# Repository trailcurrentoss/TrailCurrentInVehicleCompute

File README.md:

# TrailCurrent In-Vehicle Compute

Dockerized edge gateway with MQTT broker, tile server, and local dashboards. Part of the [TrailCurrent](https://trailcurrent.com) open-source vehicle platform.

## Quick Navigation

| I want to... | Go here |
|--------------|---------|
| Set up a development environment | [Development Setup](#development-setup) below |
| Build a deployment package | [Building Deployment Packages](#building-deployment-packages) below |
| Set up a new Raspberry Pi | [DOCS/RaspberryPiOneTimeSetup.md](DOCS/RaspberryPiOneTimeSetup.md) |
| Deploy or update a Pi | [PI_DEPLOYMENT.md](PI_DEPLOYMENT.md) |
| Set up Node-RED flows | [Node-RED Setup](#node-red-setup) below |
| Understand cloud OTA updates | [OTA_DEPLOYMENT_IMPLEMENTATION.md](OTA_DEPLOYMENT_IMPLEMENTATION.md#cloud-to-pi-ota-deployment-deployment-watcher) |

## Prerequisites

- **Docker Engine** (or Docker Desktop) with the `compose` plugin and `buildx`
- **Git**

---

## Development Setup

This gets your local development environment running with hot-reload and debugging enabled. All services build from local Dockerfiles for the host platform.

### Step 1: Clone and configure environment

```bash
git clone <REPO_URL>
cd TrailCurrentInVehicleCompute
git config core.hooksPath .githooks
docker buildx use default
cp .env.example .env
```

### Step 2: Generate secure random values

```bash
# Generate ENCRYPTION_KEY (64 character hex string)
openssl rand -hex 32

# Generate NODE_RED_CREDENTIAL_SECRET (128 character hex string)
openssl rand -hex 64
```

Copy these values into the corresponding fields in `.env`.

### Step 3: Edit `.env` and set your values

- `NODE_RED_ADMIN_USER` - Your Node-RED admin username
- `NODE_RED_ADMIN_PASSWORD` - Your desired admin password (plain text - auto-hashed at startup)
- `ENCRYPTION_KEY` - Paste the value from step 2
- `NODE_RED_CREDENTIAL_SECRET` - Paste the value from step 2
- `ADMIN_PASSWORD` - Strong password for system admin access
- `MQTT_USERNAME` - Username for MQTT broker
- `MQTT_PASSWORD` - Password for MQTT broker (plain text - auto-added to broker at startup)
- `TLS_CERT_HOSTNAME` - Your device's hostname (e.g., `trailcurrent01.local`)

### Step 4: Generate SSL certificates

```bash
./scripts/generate-certs.sh
# Select option 1 for Development or option 2 for Production
```

See [SSL Certificate Generation](#ssl-certificate-generation) for details.

### Step 5: Obtain map tiles

The tileserver requires a pre-generated mbtiles file to serve map data.

```bash
mkdir -p data/tileserver
# Place your tiles file at: data/tileserver/map.mbtiles
```

To generate tiles from OpenStreetMap data, use the **PbfTileConverter** utility:
[../../Utilities/PbfTileConverter](../../Utilities/PbfTileConverter)

Or copy `map.mbtiles` from an existing team member's machine.

### Step 6: Build and start in development mode

```bash
docker compose -f docker-compose.yml -f docker-compose.dev.yml up -d --build
```

The `--build` flag ensures all images are built from local Dockerfiles for your host platform. Development mode enables:
- Hot-reload for frontend and backend code changes
- Node.js debug port (9229) for VSCode debugger attachment
- MongoDB accessible on localhost:27017
- Node-RED accessible on localhost:1880
- Tileserver styles hot-reload

Containers will automatically:
- Generate the bcrypt hash for Node-RED from your plain password
- Create the mosquitto password file from your credentials
- Initialize all services with consistent credentials
- Mount the SSL certificates for HTTPS/MQTTS communication
- Load map tiles from the mbtiles file

### Verification Checklist

After startup, verify all services are healthy:

```bash
# All 7 containers should be running
docker compose ps

# Frontend loads
curl -k https://localhost/

# Tileserver healthy
curl http://localhost:8080/health

# Map style served
curl -s http://localhost:8080/styles/3d-dark/style.json | head -5

# Font glyphs available
curl -s -o /dev/null -w "%{http_code}" "http://localhost:8080/fonts/Noto%20Sans%20Regular/0-255.pbf"
# Expected: 200
```

**Access the web UI:** https://localhost (accept the self-signed certificate warning)

### Security Notes

- `.env` is in `.gitignore` - will never be committed
- Use strong, randomly generated passwords for all credentials
- All values in `.env.example` are placeholders only
- Passwords are auto-hashed/auto-configured at container startup

---

## Building Deployment Packages

For creating the offline zip that gets deployed to Raspberry Pis. The deployment pipeline builds Docker images for ARM64, packages them as tar files, and creates a self-contained zip.

```bash
# Build everything and create the zip
./create-deployment-package.sh --version=1.0.0
```

This will:
1. Build all 6 service images for `linux/arm64` (plus pull `mongo:7`)
2. Save images as `.tar` files in `images/`
3. Fetch MCU firmware from GitHub releases (if available)
4. Package everything into `trailcurrent-deployment-1.0.0.zip`

**Transfer and deploy to Pi:**
```bash
scp trailcurrent-deployment-1.0.0.zip trailcurrent@pi.local:~
# On the Pi:
unzip trailcurrent-deployment-1.0.0.zip && chmod +x deploy.sh && ./deploy.sh
```

See [PI_DEPLOYMENT.md](PI_DEPLOYMENT.md) for detailed deployment instructions.

---

## Project Structure

```
containers/          Dockerfiles for each service
  frontend/          nginx + MapLibre GL web UI
  backend/           Node.js Express API
  mosquitto/         Eclipse Mosquitto MQTT broker
  node-red/          Node-RED flow engine
  noderedproxy/      nginx HTTPS proxy for Node-RED
  tileserver/        Custom tile server (styles, fonts, sprites)
config/              Version-controlled service configurations
  mosquitto/         mosquitto.conf
  node-red/          settings.js, starter-flow.json, cloud-workflow.json
data/                Runtime data (gitignored)
  keys/              TLS certificates
  tileserver/        map.mbtiles
  node-red/          Node-RED flows
local_code/          Python host services (CAN-to-MQTT bridge, deployment watcher, OTA helpers)
scripts/             Utility scripts (cert generation)
```

**Docker Compose files:**
- `docker-compose.yml` — Production orchestration (7 services)
- `docker-compose.dev.yml` — Development overrides (hot-reload, debug ports)

---

## SSL Certificate Generation

The application uses TLS/SSL for secure communication. Certificates must be generated before running `docker compose up`. The `scripts/generate-certs.sh` script supports two modes:

### Quick Reference

```bash
# Interactive mode (prompts for selection)
./scripts/generate-certs.sh

# Non-interactive mode (development)
./scripts/generate-certs.sh 1

# Non-interactive mode (production)
./scripts/generate-certs.sh 2

# Using environment variable
CERT_MODE=2 ./scripts/generate-certs.sh

# Show help
./scripts/generate-certs.sh --help
```

### Development Certificates (Local Testing)

For local development with `localhost` or `127.0.0.1`:

```bash
./scripts/generate-certs.sh 1
```

**Development certificates include:**
- DNS names: `localhost`, plus your `TLS_CERT_HOSTNAME` from `.env`
- IP addresses: `127.0.0.1`, `::1` (IPv6 localhost)

**Access locally:**
```
https://localhost           - Frontend (HTTPS)
https://localhost:8443      - Node-RED (HTTPS)
```

Accept the self-signed certificate warning in your browser (one-time).

### Production Certificates (Deployment)

For deployed devices accessed from other machines on the network:

1. **Set your device's hostname** in `.env`:
   ```
   TLS_CERT_HOSTNAME=trailcurrent01.local
   ```

2. **Generate production certificates:**
   ```bash
   ./scripts/generate-certs.sh 2
   ```

3. **Install the CA certificate** (`data/keys/ca.crt`) on devices that will access the web UI.

4. **Access from the network:**
   ```
   https://trailcurrent01.local       - Web UI
   mqtts://trailcurrent01.local:8883  - MQTT broker
   ```

### Regenerating Certificates

Run the script anytime to regenerate. It will prompt before overwriting existing certificates and create backups.

```bash
./scripts/generate-certs.sh
docker compose restart
```

Certificates are automatically protected by `.gitignore`. Never commit them to version control.

---

## Docker

### Running Containers

```bash
# Development mode (hot-reload, debug ports) — always use --build to ensure local images
docker compose -f docker-compose.yml -f docker-compose.dev.yml up -d --build

# Production mode (after verification)
docker compose up -d --build
```

### Docker Networking

**MongoDB Access:**
- Services communicate via Docker's internal network: `mongodb:27017`
- MongoDB is NOT exposed to localhost (127.0.0.1)
- To access MongoDB from your host: `docker compose exec mongodb mongosh`

Docker containers use service names for inter-container communication.

### Data Persistence

The `data/` directory contains all persistent application data:

- **SSL certificates** (`data/keys/`) — Generated once, valid for 10 years
- **Map tiles** (`data/tileserver/map.mbtiles`) — Set up once, rarely updated
- **Node-RED flows** (`data/node-red/`) — User-created flows and settings
- **MongoDB** — Named volume `mongodb-data`, persists across rebuilds

**Never delete `data/` during updates** unless performing a complete reset. All data persists across container rebuilds.

**Updating the Application (No Data Loss):**
```bash
git pull
docker compose -f docker-compose.yml -f docker-compose.dev.yml up -d --build
# Certificates, .env, map tiles, and Node-RED flows are preserved
```

---

## Node-RED Setup

Node-RED bridges CAN bus messages to local MQTT topics that the PWA consumes. Flow templates are stored in `config/node-red/`.

### What the Starter Flow Does

- **Inbound:** Subscribes to `can/inbound`, routes by CAN identifier, and publishes parsed data to `local/*` topics:
  - Light status (8 channels) → `local/lights/{1-8}/status`
  - Temperature & humidity → `local/airquality/temphumid`
  - GPS coordinates, altitude, details, time → `local/gps/*`
- **Outbound:** Subscribes to `local/lights/{1-8}/command` (from PWA light toggles) and sends CAN messages to `can/outbound`
- **Test controls:** Manual inject nodes for toggling lights, setting brightness, and all-on/all-off

### Automatic Loading (First Startup)

On first startup, the backend automatically detects that Node-RED has no flows and injects the starter flow via the Node-RED Admin API. Existing installations with flows already present are not affected.

### Cloud Workflow (Auto-Injected)

When cloud synchronization is enabled in Settings, the backend automatically injects a "Cloud Workflow" tab into Node-RED that bridges messages between the local and cloud MQTT brokers:

- **Cloud → Local (Commands):** `rv/lights/N/command` → CAN toggle, `rv/thermostat/command` → local passthrough
- **Local → Cloud (Status):** Light status, air quality, GPS, energy, thermostat — each rate-limited to 30 msg/sec

The cloud workflow is automatically removed when cloud is disabled or the system config is reset. The template is at `config/node-red/cloud-workflow.json`.

### Manual Import (Existing Installations)

1. Open Node-RED at `https://<hostname>:8443`
2. Click the hamburger menu (top right) → **Import**
3. Select **Upload** and choose `config/node-red/starter-flow.json`
4. Click **Import**

### Configure MQTT Credentials

After importing, Node-RED needs MQTT credentials to connect to Mosquitto:

1. Double-click any MQTT node (e.g. "CAN Inbound")
2. Click the pencil icon next to **Local MQTT Broker**
3. Go to the **Security** tab
4. Enter your `MQTT_USERNAME` and `MQTT_PASSWORD` (same values from `.env`)
5. Click **Update**, then click the red **Deploy** button

The broker is pre-configured to connect to `mosquitto:8883` via Docker internal DNS with TLS.

---

## Debugging

### VSCode Node.js Debugger

The backend Node.js server can be debugged using VSCode's built-in debugger. The setup uses `--inspect-brk` to pause the application at startup, waiting for the debugger to attach before continuing execution.

#### Quick Start

1. **Open the project in VSCode** (if not already open)

2. **Start debugging:**
   - Open the Debug panel (Ctrl+Shift+D / Cmd+Shift+D)
   - Select "Backend Debug" from the dropdown
   - Click the green "Start Debugging" button (or press F5)

3. **What happens automatically:**
   - Docker containers start in development mode (`docker-compose -f docker-compose.yml -f docker-compose.dev.yml up`)
   - Backend container starts with `--inspect-brk=0.0.0.0:9229` (pauses at startup)
   - VSCode automatically attaches the debugger to port 9229
   - Application resumes and you can now set breakpoints

4. **Stop debugging:**
   - Press Shift+F5 or click the stop button in the debug panel
   - Docker containers are automatically stopped (`docker-compose down`)

#### Manual Debugging (Without VSCode Integration)

```bash
# Start containers in development mode
docker compose -f docker-compose.yml -f docker-compose.dev.yml up

# In VSCode, attach manually:
# - Open Debug panel (Ctrl+Shift+D)
# - Select "Backend Debug"
# - Click "Start Debugging" (F5)
```

#### Debugging Configuration

The debugging setup is configured in `.vscode/launch.json`:

```json
{
  "name": "Backend Debug",
  "type": "node",
  "request": "attach",
  "port": 9229,
  "address": "localhost",
  "restart": true,
  "skipFiles": ["<node_internals>/**"],
  "outFiles": ["${workspaceFolder}/containers/backend/src/**/*.js"]
}
```

#### Troubleshooting

**"Connection refused" error:**
- Ensure containers are running: `docker compose ps`
- Check backend container logs: `docker compose logs backend`
- Verify port 9229 is exposed: `docker compose port backend 9229`

**Breakpoints not being hit:**
- Verify the file path matches exactly (case-sensitive on Linux)
- Check development mode: `docker compose config | grep "NODE_ENV"`

**Backend container exits immediately:**
- Check logs: `docker compose logs backend`
- Ensure `.env` file is set up correctly
- Verify MongoDB: `docker compose logs mongodb`

**Mosquitto or other containers failing to start:**
- Check logs: `docker compose logs mosquitto`
- Certificate permissions: `chmod 644 data/keys/*.key data/keys/*.crt data/keys/*.pem`

**Port conflicts:**
- Clean up: `docker system prune -f --volumes`
- Verify no containers running: `docker ps -a`
- Restart Docker: `sudo systemctl restart docker`

#### Tips for Effective Debugging

1. **Breakpoint in startServer()** in `src/index.js` to debug initialization
2. **Route breakpoints** in route handlers (e.g., `src/routes/thermostat.js`)
3. **MQTT debugging** via breakpoints in `src/mqtt.js`
4. **Database debugging** via breakpoints in `src/db/init.js`
5. **Conditional breakpoints**: Right-click a breakpoint to set conditions
6. **Logpoints**: Right-click line number to log values without pausing

---

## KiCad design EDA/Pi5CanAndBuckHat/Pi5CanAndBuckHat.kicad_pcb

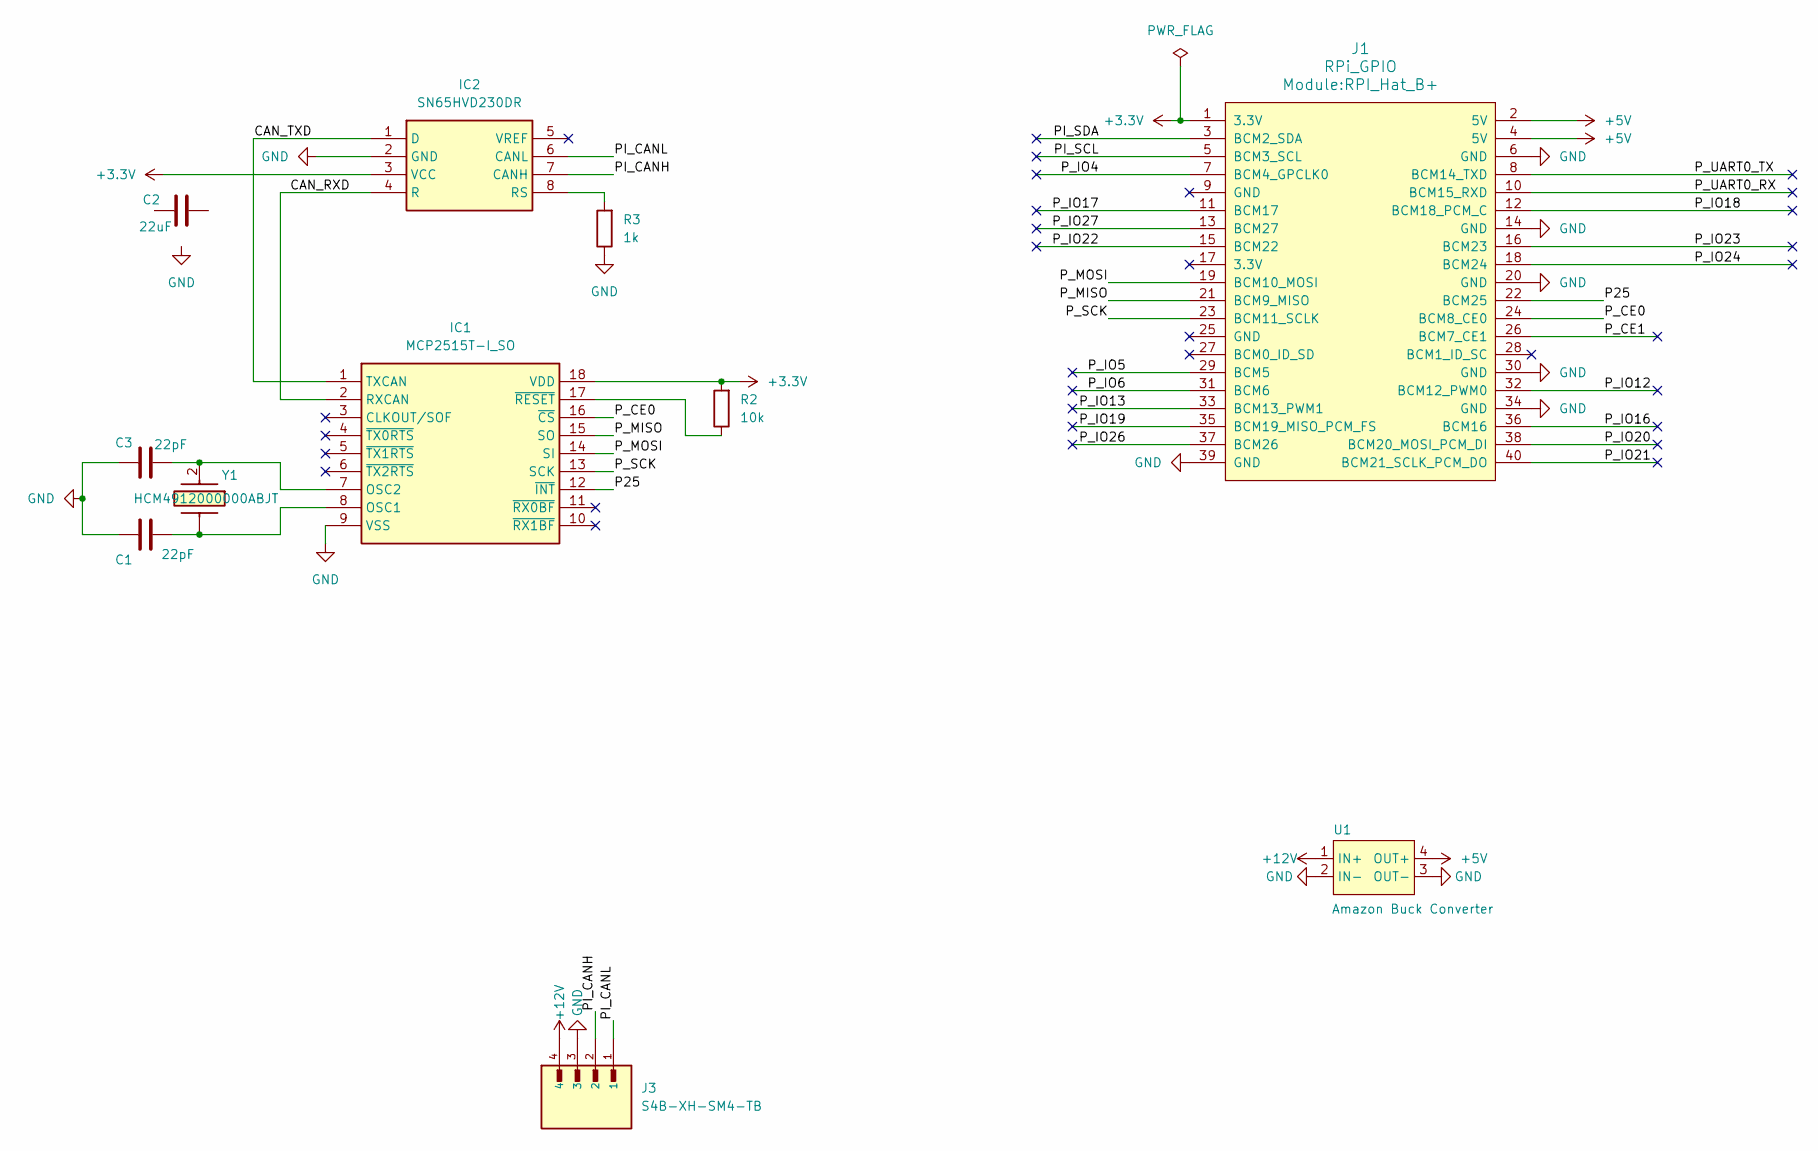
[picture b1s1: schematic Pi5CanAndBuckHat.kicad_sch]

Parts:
C1, C3: 22pF; C_1206_3216Metric
C2: 22uF; C_1206_3216Metric
IC1: MCP2515T-I_SO; MCP2515T-ISO; Mouser Part Number 579-MCP2515T-I/SO
IC2: SN65HVD230DR; Mouser Part Number 595-SN65HVD230DR
J1: RPi_GPIO; RPI_Hat_B+
J3: S4B-XH-SM4-TB; JST_S4B-XH-SM4-TB; LCSC Part C161861
R2: 10k; R_1206_3216Metric
R3: 1k; R_1206_3216Metric
U1: Amazon Buck Converter; AmazonBuckConverter
Y1: HCM4912000000ABJT; Mouser Part Number 695-HCM4912.0ABJT

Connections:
+3.3V: IC1.18 (VDD), IC2.3 (VCC), J1.1 (3.3V), R2.2
+5V: J1.2 (5V), J1.4 (5V), U1.4 (OUT+)
+12V: J3.4, U1.1 (IN+)
/CAN_RXD: IC1.2 (RXCAN), IC2.4 (R)
/CAN_TXD: IC1.1 (TXCAN), IC2.1 (D)
/P25: IC1.12 (~INT), J1.22 (BCM25)
/PI_CANH: IC2.7 (CANH), J3.2
/PI_CANL: IC2.6 (CANL), J3.1
/PI_SCL: J1.5 (BCM3_SCL)
/PI_SDA: J1.3 (BCM2_SDA)
/P_CE0: IC1.16 (~CS), J1.24 (BCM8_CE0)
/P_CE1: J1.26 (BCM7_CE1)
/P_IO4: J1.7 (BCM4_GPCLK0)
/P_IO5: J1.29 (BCM5)
/P_IO6: J1.31 (BCM6)
/P_IO12: J1.32 (BCM12_PWM0)
/P_IO13: J1.33 (BCM13_PWM1)
/P_IO16: J1.36 (BCM16)
/P_IO17: J1.11 (BCM17)
/P_IO18: J1.12 (BCM18_PCM_C)
/P_IO19: J1.35 (BCM19_MISO_PCM_FS)
/P_IO20: J1.38 (BCM20_MOSI_PCM_DI)
/P_IO21: J1.40 (BCM21_SCLK_PCM_DO)
/P_IO22: J1.15 (BCM22)
/P_IO23: J1.16 (BCM23)
/P_IO24: J1.18 (BCM24)
/P_IO26: J1.37 (BCM26)
/P_IO27: J1.13 (BCM27)
/P_MISO: IC1.15 (SO), J1.21 (BCM9_MISO)
/P_MOSI: IC1.14 (SI), J1.19 (BCM10_MOSI)
/P_SCK: IC1.13 (SCK), J1.23 (BCM11_SCLK)
/P_UART0_RX: J1.10 (BCM15_RXD)
/P_UART0_TX: J1.8 (BCM14_TXD)
GND: C1.1, C3.1, IC1.9 (VSS), IC2.2 (GND), J1.6 (GND), J1.14 (GND), J1.20 (GND), J1.30 (GND), J1.34 (GND), J1.39 (GND), J3.3, R3.1, U1.2 (IN-), U1.3 (OUT-)
unnamed: C1.2, IC1.8 (OSC1), Y1.
unnamed: C3.2, IC1.7 (OSC2), Y1.2 (CRYSTAL_2)
unnamed: IC1.17 (~RESET), R2.1
unnamed: IC2.8 (RS), R3.2

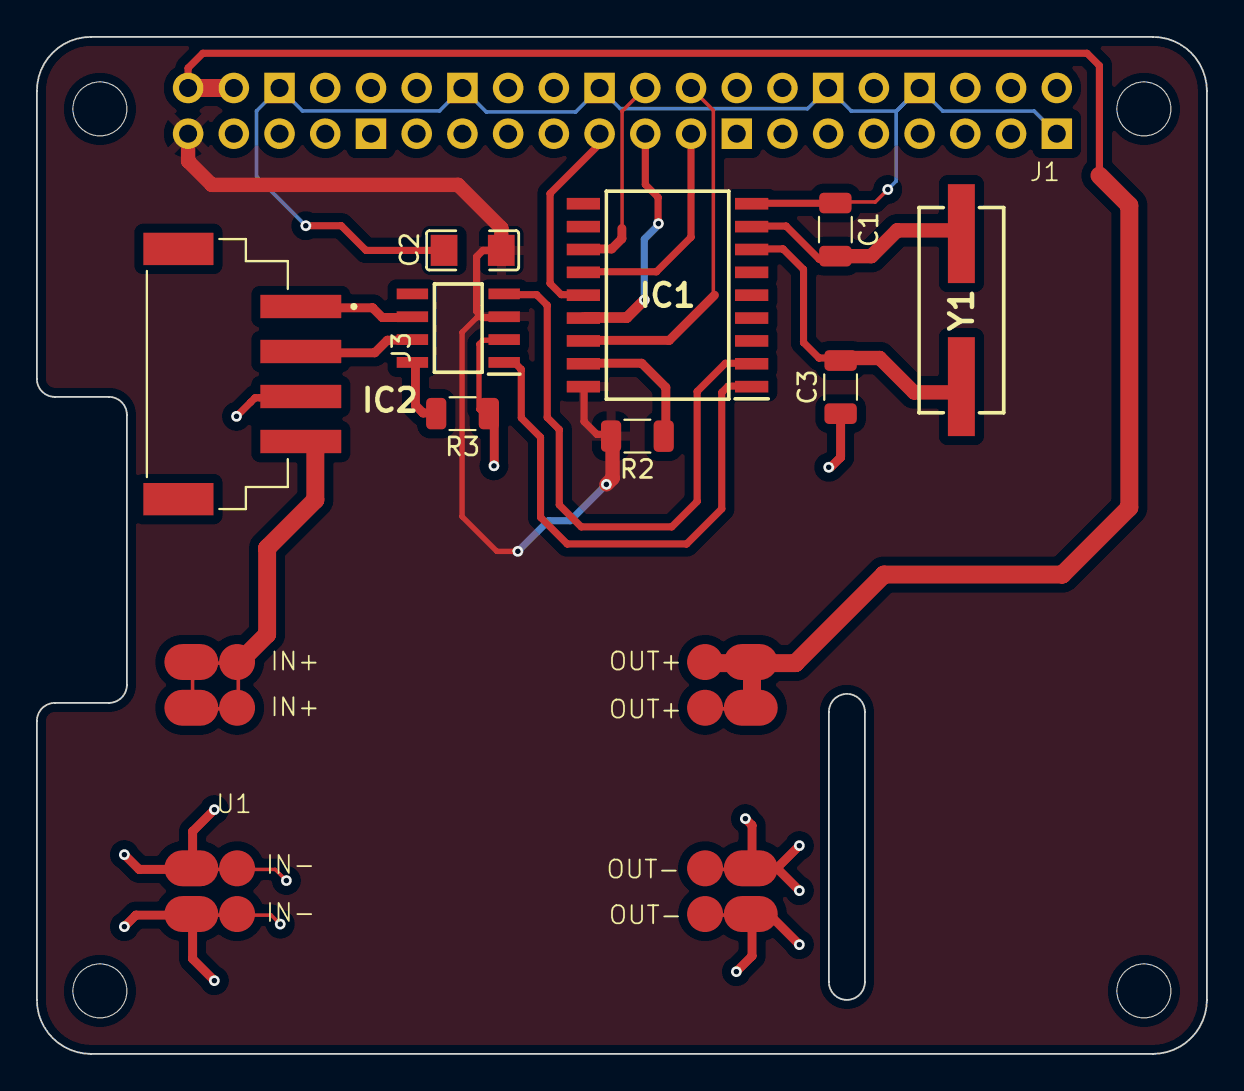
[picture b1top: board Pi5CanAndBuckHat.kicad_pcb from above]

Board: 2 copper layers, 65.0 x 56.5 mm, 11 parts (0 on the bottom side), 17 nets.

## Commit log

2026-02-12 Initial commit: Clean migration to public Codeberg repository
    This is a fresh start on Codeberg with all security and configuration
    issues addressed:
    Security fixes:
    - Removed all git history (fresh start)
    - No personal paths or credentials exposed
    - All WiFi secrets in .gitignore (using secrets.h.example pattern)
2026-02-12 Add .vscode/ to .gitignore
2026-02-14 Adding license file
2026-02-15 WIP Initial Pi setup and script for zip deploy
2026-02-15 Continued work on initial setup doc
2026-02-15 Setup work
2026-02-16 Screnshot added
2026-02-16 Fixing bug with Wifi credentials being sent over CAN frames
2026-02-17 Edit settings brought in
2026-02-17 Temp commit while moving to new pi imager instructions
2026-02-17 Docs update with new pi imager instructions in the correct order
2026-02-17 Updated docs based on latest test run
2026-02-17 Progress on documentation for one time pi setup. Still finalizing verification steps. May need additional changes.
2026-02-17 Documentation updates
2026-02-17 Validating initial setup documentation and switching to map.mbtiles naming convention
2026-02-18 Fix new contributor onboarding: commit fonts, restructure docs
    - Commit 10 font families (Noto Sans, Roboto, Metropolis) directly to repo
    (all licenses permit commercial use: OFL, Apache 2.0, Unlicense)
    - Rewrite setup.sh as verification tool (remove hardcoded paths)
    - Add font pre-check to build-and-save-images.sh
    - Restructure README.md with clear 6-step dev setup and verification checklist
    - Remove stale README sections (non-existent containers, manual password gen)
2026-02-18 Add pre-commit hooks to keep the repository agentic agnostic
2026-02-18 Updates to documentation for new develoeprs. County boundarires removed from maps. ARM and X64 builds documented.
2026-02-18 Removing old documentation
2026-02-18 Fixing script that builds the zip file for the Pi
2026-02-18 Validated new contributor setup all the way to building and deploying zip to raspberry pi
2026-02-18 Automated service reegistry on first time setups of new raspbery pis
2026-02-19 Added starter workflow and updated compose volumes so that a local workflow is available upon first deployment.
2026-02-19 Revised first run instructions
2026-02-20 Logo added to case cover, 3mf added to store orientation for printing.
2026-02-20 Documentation updates after the changes for the node-red OOB flow
2026-02-20 Updated documentation and scripts to match ~/ root deployment pattern.
2026-02-20 Fixes for CA path on the python code for connection to MQTT. Kept separate from containers keys to avoid ownership conflicts.
2026-02-20 Final verified setup of initial Pi configuration
2026-02-20 One confirmed zip deploy with firmware for PDM
2026-02-22 Changes for deploying from zip uploaded to the cloud
2026-02-22 Deployment tested end to end
2026-02-22 Removing old firmeware before applying new update
2026-02-22 Applying fix for older docker tar files during deployment
2026-02-22 Updated logos and fixes to service worker for missing files
2026-02-22 Updating old icon for app and launch screens
2026-02-22 Fix iOS PWA icon showing 'T' monogram instead of app icon
2026-02-22 Fixed script deploying firmware when left from previous releases. Icons updated.
2026-02-22 Caching issue resolved and instructions for how to install generated CA cert on various devices
2026-02-22 Fixing certificate expiry issues that will solve trust issues on IOS
2026-02-22 More CA fixes and updates to deploy script to remove orphan containers
2026-02-22 Working changes for certs that work with iOS
2026-02-22 node-red cloud workflow now gets populated when cloud is enabled
2026-02-22 Added rate limit to default cloud workflow
2026-02-23 Removed cloud connectivity from initial setup. Moved to config and will populate cloud workflow with rate limiters
2026-02-23 Add trailcurrent.com link to README
2026-02-25 Fixing PWA not installing and updated KiCAD EDA files to use library
2026-03-01 Updated case cover and orientation for printing cover
2026-03-01 Added configuration that updates both local PWA and the cloud PWA for control button names and icons
2026-03-01 Updated icons
2026-03-01 Toggle all on and off working
2026-03-01 Fixes for can bus timing issues on startup. Fixes to improve deploy.sh when changes exist in the service itself.
2026-03-01 Handle data coming and going when modules are connected and disconnected "-" will display when connectivity is lost
2026-03-01 Improving cloud deployment to get status
2026-03-01 Improved logging and error handling during OTA
2026-03-01 Fixes for stuck deployment watcher in loop
2026-03-01 More bug fixes for race conditions
2026-03-01 Verified status updates to the cloud during OTA
2026-03-02 Fix for error in deployment watcher when DNS wasn't available yet
2026-03-03 Updated start flow to be named so it can be udpated by OTA as well
2026-03-03 Fixing status changes for labels updating so they will appear as they happen
2026-03-04 Updated node-red start flow to have the data for SOC, voltage, wattage and other power fields
